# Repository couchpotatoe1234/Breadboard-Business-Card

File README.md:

## Breadboard Business Card
This is a simple fun project that I had in mind that is a way to connect an ATTINY85 to a breadboard and have something cool to show of to others as a fist impression or something. It is a really simple 90mmx50mm rectangle with the ATTINY85 in the middle with traces fanning out to holes for pinheaders. This was designed using KiCad. 
Heres the BOM
| Name                 | Purpose                                  | Quantity | Total Cost (USD) | Link                                                                                                                                                                                                                                                                             | Distributor |
|----------------------|------------------------------------------|----------|------------------|----------------------------------------------------------------------------------------------------------------------------------------------------------------------------------------------------------------------------------------------------------------------------------|-------------|
| USB-C breakout board | to program the microcontroller via USB-C | 1        | 2.95             | https://www.digikey.com/en/products/detail/adafruit-industries-llc/4090/9951930?gclsrc=aw.ds&gad_source=1&gad_campaignid=20783325532&gbraid=0AAAAADrbLlhQ0SDH8McA_eU18OaEfPdt4&gclid=CjwKCAjwnZfPBhAGEiwAzg-VzMjMCdtWeSUzC-3yIatAatWLNJ1h28MdtUJpaOAKU7OeBHA8Vr8fbBoCrJwQAvD_BwE | Digikey     |
| 1x1 male pinheaders  | to connect the card to a breadboard      | 16       | 1.60             | https://www.digikey.com/en/products/detail/adam-tech/PH1-01-UA/9830231                                                                                                                                                                                                           | Digikey     |
| ATTINY85-20SU        | The microcontroller                      | 2        | 3.00             | https://www.digikey.com/en/products/detail/microchip-technology/attiny85-20su/735470                                                                                                                                                                                             | Digikey     |
| PCB                  | The main part                            | 1        | 2.00             | https://jlcpcb.com                                                                                                                                                                                                                                                               | JLCPCB      |

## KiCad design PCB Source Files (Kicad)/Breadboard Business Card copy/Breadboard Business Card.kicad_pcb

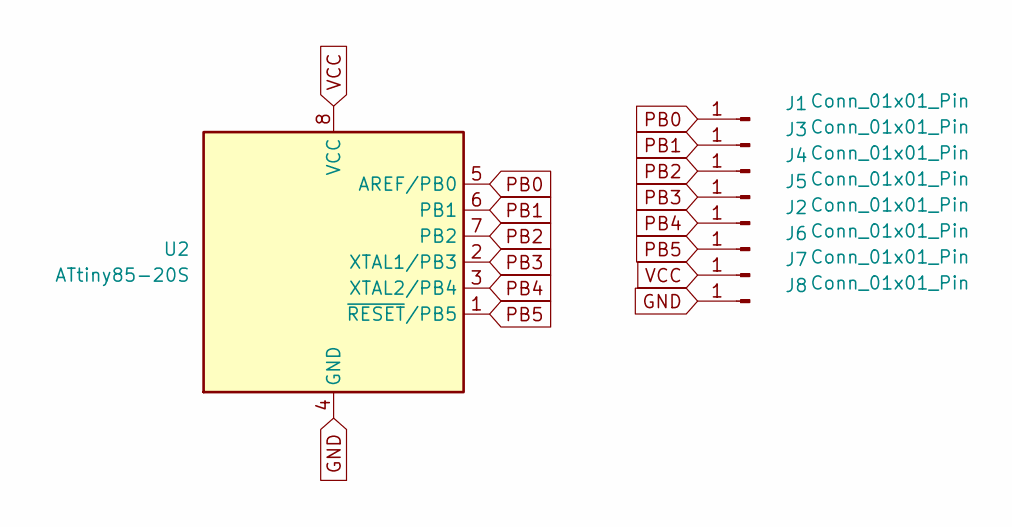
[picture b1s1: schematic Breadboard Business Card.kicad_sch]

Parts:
J1, J2, J3, J4, J5, J6, J7, J8: Conn_01x01_Pin; PinHeader_1x01_P2.54mm_Vertical
U2: ATtiny85-20S; SOIC-8_5.3x5.3mm_P1.27mm

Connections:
GND: J8.1 (Pin_1_1), U2.4 (GND)
PB0: J1.1 (Pin_1_1), U2.5 (AREF/PB0)
PB1: J3.1 (Pin_1_1), U2.6 (PB1)
PB2: J4.1 (Pin_1_1), U2.7 (PB2)
PB3: J5.1 (Pin_1_1), U2.2 (XTAL1/PB3)
PB4: J2.1 (Pin_1_1), U2.3 (XTAL2/PB4)
PB5: J6.1 (Pin_1_1), U2.1 (~RESET/PB5)
VCC: J7.1 (Pin_1_1), U2.8 (VCC)

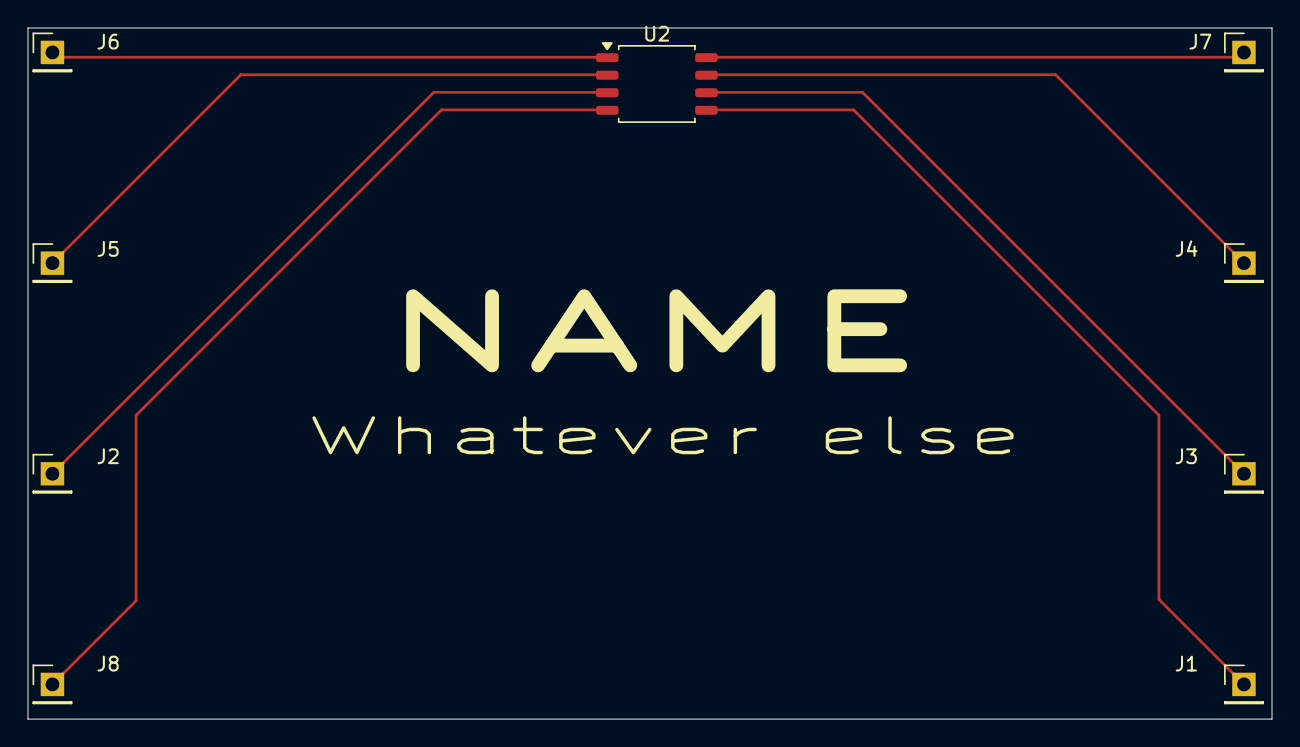
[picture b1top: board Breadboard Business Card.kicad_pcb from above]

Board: 2 copper layers, 90.0 x 50.0 mm, 9 parts (0 on the bottom side), 8 nets.

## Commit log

2026-04-21 adding source files
2026-04-21 README
2026-04-21 adding Gerbers
2026-04-21 firmware
2026-04-21 final PCB change
2026-04-21 updating firmware
